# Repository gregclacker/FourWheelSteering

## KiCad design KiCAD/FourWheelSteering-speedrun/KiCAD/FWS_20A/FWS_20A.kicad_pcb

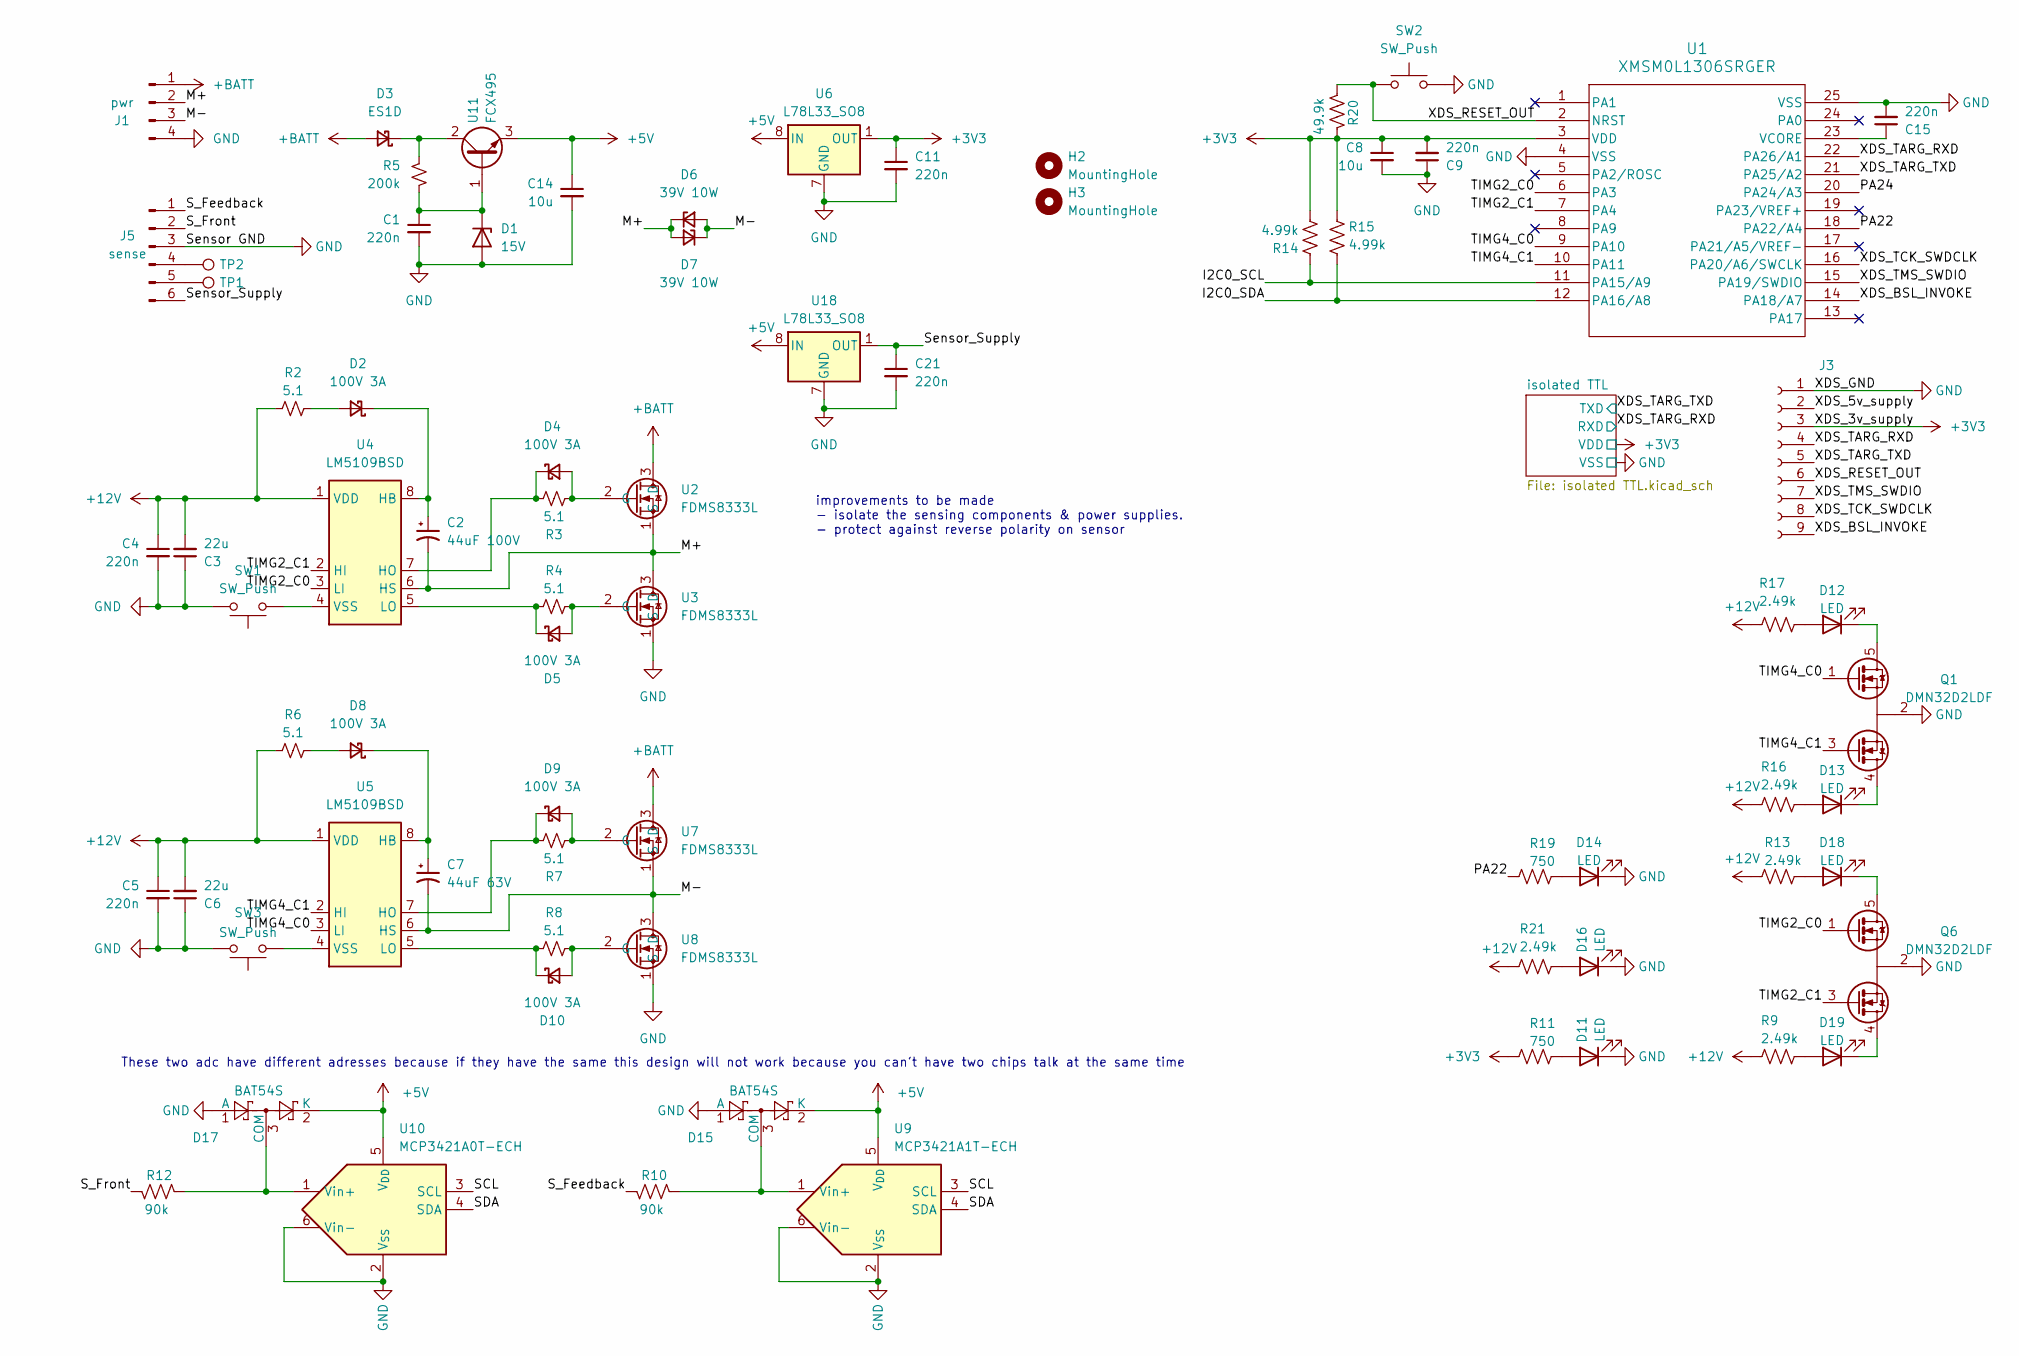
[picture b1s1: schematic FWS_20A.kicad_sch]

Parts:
C1, C4, C5, C9, C11, C15, C21: 220n; C_1206_3216Metric_Pad1.33x1.80mm_HandSolder
C2: 44uF 100V; CP_Radial_D6.3mm_P2.50mm
C3, C6: 22u; C_1206_3216Metric_Pad1.33x1.80mm_HandSolder
C7: 44uF 63V; CP_Radial_D6.3mm_P2.50mm
C8, C14: 10u; C_1206_3216Metric_Pad1.33x1.80mm_HandSolder
D1: 15V; D_SOD-123
D2, D4, D5, D8, D9, D10: 100V 3A; PMDE
D3: ES1D; D_SMA
D6, D7: 39V 10W; D_SMC_Handsoldering
D11, D12, D13, D14, D16, D18, D19: LED; LED_0603_1608Metric
D15, D17: BAT54S; SOT-23-3
H2, H3: MountingHole; MountingHole_2.2mm_M2_DIN965
J1: pwr; SolderWire-0.75sqmm_1x04_P4.8mm_D1.25mm_OD2.3mm
J3: Conn_01x09_Socket; PinHeader_1x09_P2.54mm_Vertical
J5: sense; Molex_Micro-Fit_3.0_43045-0600_2x03_P3.00mm_Horizontal
Q1, Q6: DMN32D2LDF; SOT-353_SC-70-5
R2, R3, R4, R6, R7, R8: 5.1; R_1206_3216Metric_Pad1.30x1.75mm_HandSolder
R5: 200k; R_0805_2012Metric_Pad1.20x1.40mm_HandSolder
R9, R13, R16, R17, R21: 2.49k; R_0603_1608Metric
R10, R12: 90k; R_1206_3216Metric_Pad1.30x1.75mm_HandSolder
R11, R19: 750; R_1206_3216Metric_Pad1.30x1.75mm_HandSolder
R14, R15: 4.99k; R_1206_3216Metric_Pad1.30x1.75mm_HandSolder
R20: 49.9k; R_1206_3216Metric_Pad1.30x1.75mm_HandSolder
SW1, SW3: SW_Push; SW_Push_SPST_NO_Alps_SKRK
SW2: SW_Push; SW_SPST_PTS645Sx43SMTR92
TP1, TP2: TestPoint; TestPoint_Loop_D2.50mm_Drill1.0mm_LowProfile
U1: XMSM0L1306SRGER; VQFN24_RGE_TEX
U2, U3, U7, U8: FDMS8333L; Power 56
U4, U5: LM5109BSD; WSON-8-1EP_4x4mm_P0.8mm_EP2.6x3mm
U6, U18: L78L33_SO8; SOIC-8_3.9x4.9mm_P1.27mm
U9: MCP3421A1T-ECH; SOT-23-6
U10: MCP3421A0T-ECH; SOT-23-6
U11: FCX495; SOT-89-3

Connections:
+3V3: C8.1, C9.2, C11.1, J3.3, R11.2, R14.2, R15.1, R20.1, U1.3 (VDD), U6.1 (OUT); also elsewhere on the board
+5V: C14.1, D15.2 (K), D17.2 (K), U6.8 (IN), U9.5 (V_{DD}), U10.5 (V_{DD}), U11.3, U18.8 (IN)
+12V: C3.2, C4.1, C5.1, C6.2, R2.2, R6.2, R9.2, R13.2, R16.2, R17.2, R21.2, U4.1 (VDD), U5.1 (VDD)
+BATT: D3.2 (A), J1.1, U2.3 (D), U7.3 (D)
/I2C0_SCL: R14.1, U1.11 (PA15/A9)
/I2C0_SDA: R15.2, U1.12 (PA16/A8)
/M+: C2.2, D6.1 (K), D7.2 (A), J1.2, U2.1 (S), U3.3 (D), U4.6 (HS)
/M-: C7.2, D6.2 (A), D7.1 (K), J1.3, U5.6 (HS), U7.1 (S), U8.3 (D)
/PA22: R19.2, U1.18 (PA22/A4)
/PA24: U1.20 (PA24/A3)
/SCL: U9.3 (SCL), U10.3 (SCL)
/SDA: U9.4 (SDA), U10.4 (SDA)
/S_Feedback: J5.1, R10.2
/S_Front: J5.2, R12.2
/Sensor_Supply: C21.1, J5.6, U18.1 (OUT)
/TIMG2_C0: Q6.1 (G1), U1.6 (PA3), U4.3 (LI)
/TIMG2_C1: Q6.3 (G2), U1.7 (PA4), U4.2 (HI)
/TIMG4_C0: Q1.1 (G1), U1.9 (PA10), U5.3 (LI)
/TIMG4_C1: Q1.3 (G2), U1.10 (PA11), U5.2 (HI)
/XDS_5v_supply: J3.2
/XDS_BSL_INVOKE: J3.9, U1.14 (PA18/A7)
/XDS_RESET_OUT: J3.6, R20.2, SW2.1, U1.2 (NRST)
/XDS_TARG_RXD: J3.4, U1.22 (PA26/A1); also elsewhere on the board
/XDS_TARG_TXD: J3.5, U1.21 (PA25/A2); also elsewhere on the board
/XDS_TCK_SWDCLK: J3.8, U1.16 (PA20/A6/SWCLK)
/XDS_TMS_SWDIO: J3.7, U1.15 (PA19/SWDIO)
GND: C1.2, C3.1, C4.2, C5.2, C6.1, C8.2, C9.1, C11.2, C14.2, C15.2, C21.2, D1.2 (A), D11.1 (K), D14.1 (K), D15.1 (A), D16.1 (K), D17.1 (A), J1.4, J3.1, J5.3, Q1.2 (S), Q6.2 (S), SW1.2, SW2.2, SW3.2, U1.4 (VSS), U1.25 (VSS), U3.1 (S), U6.2 (GND), U6.3 (GND), U6.6 (GND), U6.7 (GND), U8.1 (S), U9.2 (V_{SS}), U9.6 (Vin-), U10.2 (V_{SS}), U10.6 (Vin-), U18.2 (GND), U18.3 (GND), U18.6 (GND), U18.7 (GND); also elsewhere on the board
unnamed: C1.1, D1.1 (K), R5.1, U11.1
unnamed: D2.2 (A), R2.1
unnamed: C2.1, D2.1 (K), U4.8 (HB)
unnamed: D3.1 (K), R5.2, U11.2
unnamed: D4.2 (A), R3.2, U2.2 (G)
unnamed: D4.1 (K), R3.1, U4.7 (HO)
unnamed: D5.2 (A), R4.1, U3.2 (G)
unnamed: D5.1 (K), R4.2, U4.5 (LO)
unnamed: D8.2 (A), R6.1
unnamed: C7.1, D8.1 (K), U5.8 (HB)
unnamed: D9.2 (A), R7.2, U7.2 (G)
unnamed: D9.1 (K), R7.1, U5.7 (HO)
unnamed: D10.2 (A), R8.1, U8.2 (G)
unnamed: D10.1 (K), R8.2, U5.5 (LO)
unnamed: D11.2 (A), R11.1
unnamed: D12.2 (A), R17.1
unnamed: D12.1 (K), Q1.5 (D1)
unnamed: D13.2 (A), R16.1
unnamed: D13.1 (K), Q1.4 (D2)
unnamed: D14.2 (A), R19.1
unnamed: D15.3 (COM), R10.1, U9.1 (Vin+)
unnamed: D16.2 (A), R21.1
unnamed: D17.3 (COM), R12.1, U10.1 (Vin+)
unnamed: D18.2 (A), R13.1
unnamed: D18.1 (K), Q6.5 (D1)
unnamed: D19.2 (A), R9.1
unnamed: D19.1 (K), Q6.4 (D2)
unnamed: J5.4, TP2.1
unnamed: J5.5, TP1.1
unnamed: SW1.1, U4.4 (VSS), U4.9 (VSS)
unnamed: SW3.1, U5.4 (VSS), U5.9 (VSS)
unnamed: C15.1, U1.23 (VCORE)

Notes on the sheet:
These two adc have different adresses because if they have the same this design will not work because you can't have two chips talk at the same time
improvements to be made - isolate the sensing components & power supplies. - protect against reverse polarity on sensor

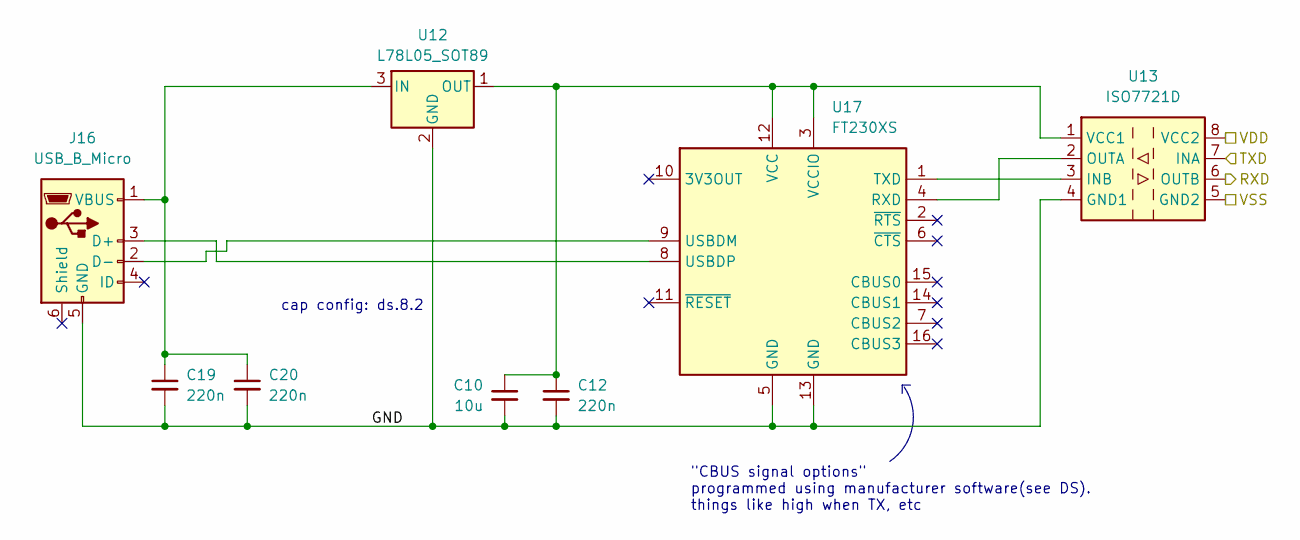
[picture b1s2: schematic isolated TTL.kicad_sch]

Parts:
C10: 10u; C_1206_3216Metric_Pad1.33x1.80mm_HandSolder
C12, C19, C20: 220n; C_1206_3216Metric_Pad1.33x1.80mm_HandSolder
J16: USB_B_Micro; USB_Micro-B_Amphenol_10118194-0001LF_Horizontal
U12: L78L05_SOT89; SOT-89-3
U13: ISO7721D; SOIC-8_3.9x4.9mm_P1.27mm
U17: FT230XS; SSOP-16_3.9x4.9mm_P0.635mm

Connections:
+3V3: U13.8 (VCC2); also elsewhere on the board
/XDS_TARG_RXD: U13.6 (OUTB); also elsewhere on the board
/XDS_TARG_TXD: U13.7 (INA); also elsewhere on the board
/isolated TTL/GND: C10.2, C12.2, C19.2, C20.2, J16.5 (GND), U12.2 (GND), U13.4 (GND1), U17.5 (GND), U17.13 (GND)
GND: U13.5 (GND2); also elsewhere on the board
unnamed: J16.3 (D+), U17.8 (USBDP)
unnamed: J16.2 (D-), U17.9 (USBDM)
unnamed: C19.1, C20.1, J16.1 (VBUS), U12.3 (IN)
unnamed: C10.1, C12.1, U12.1 (OUT), U13.1 (VCC1), U17.3 (VCCIO), U17.12 (VCC)
unnamed: U13.3 (INB), U17.1 (TXD)
unnamed: U13.2 (OUTA), U17.4 (RXD)

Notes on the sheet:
"CBUS signal options" programmed using manufacturer software(see DS). things like high when TX, etc
cap config: ds.8.2

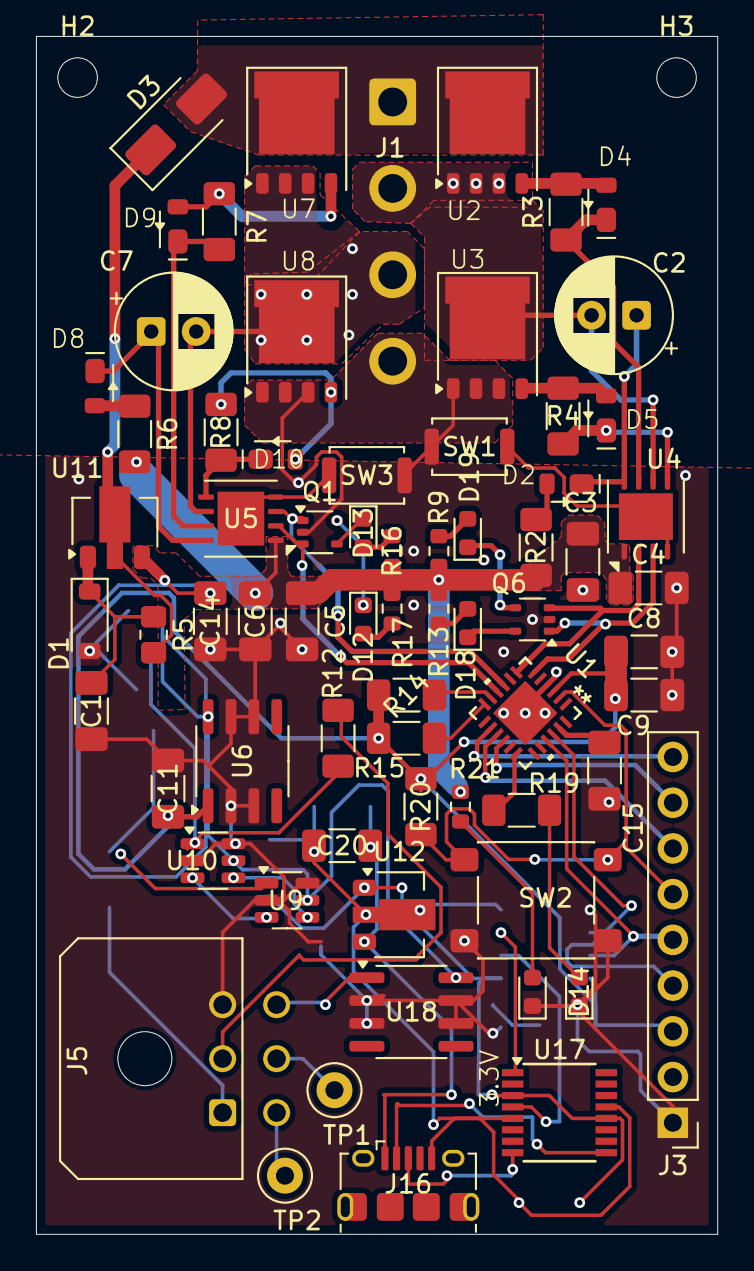
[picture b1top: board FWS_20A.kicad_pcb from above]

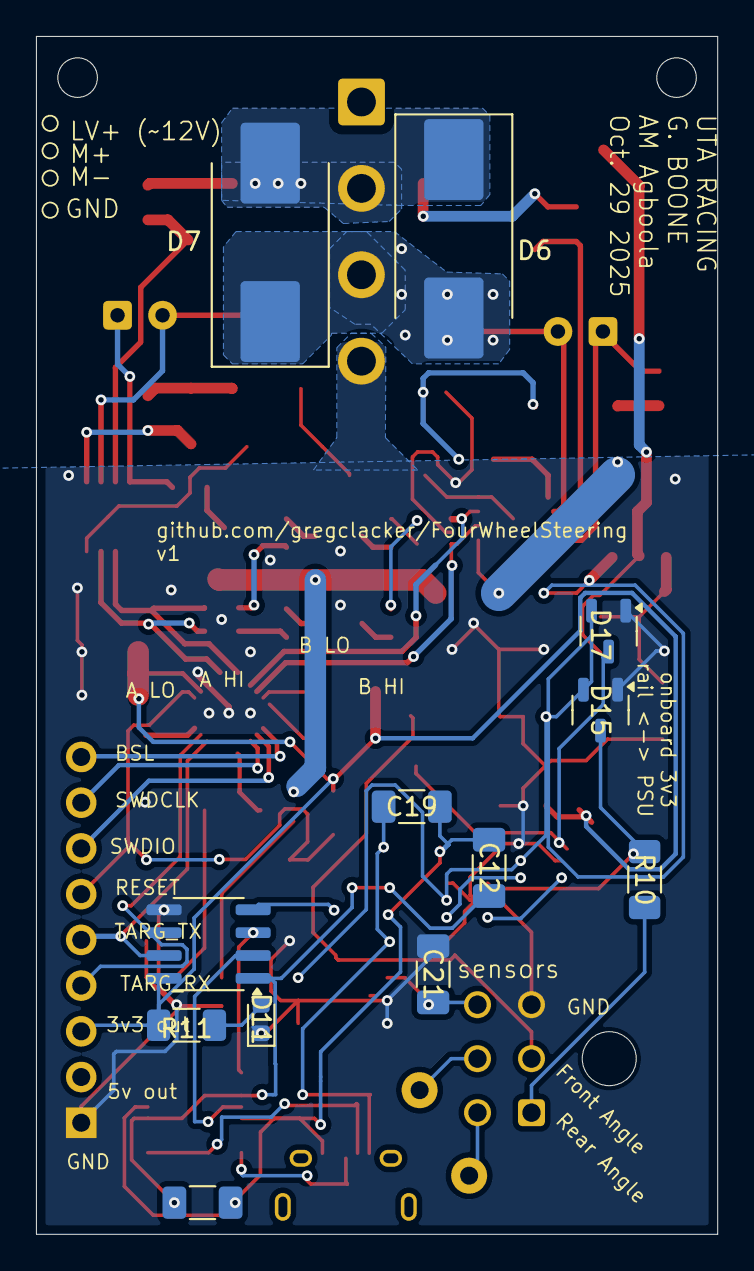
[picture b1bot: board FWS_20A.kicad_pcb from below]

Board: 2 copper layers, 37.8 x 66.5 mm, 83 parts (12 on the bottom side), 64 nets.

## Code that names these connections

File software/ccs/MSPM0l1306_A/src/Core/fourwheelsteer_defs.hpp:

/*
 * fourwheelsteer_defs.hpp
 *
 *  Created on: Nov 25, 2025
 *      Author: FSAE
 *      Drived From: https://github.com/gregclacker/FourWheelSteering/tree/main/original%20VSC%20project
 *      Contributer: Marcus Turley, Abdul-Muizz Abgoola
 */

#include <stdint.h>
#include <stdbool.h>

#include "system.hpp"

#ifndef system
#define system

/*************************************************************/

#define ESP_OK 0

//TIMG0_C0, TIMG0_C1, TIMG4_C0, TIMG4_C0
#define GATE_PIN_1         System::GPIO::PA3
#define GATE_PIN_2         System::GPIO::PA4

#define GATE_PIN_3         System::GPIO::PA10
#define GATE_PIN_4         System::GPIO::PA11

#define TIMERSYNC_REG           TIMG0
#define TIMER_REG_1             TIMG2
#define TIMER_REG_2             TIMG4

#define ADC_1_ADDR              0x49 // TODO: Update this address to match adc
#define ADC_2_ADDR              0x50

namespace System { namespace GPIO { } }

namespace FWS_Utils {

    /* NB - All this stuff is derived from the FourwheelSteering github we forked:
     * The github contains helpful front and rear wheel steer math for angles
     */
    namespace FWS {

        typedef struct {
            double WA_LW_Slope;             //This is the slope of the left wheel, wheel angle vs turn radius
            double WA_LW_Intercept;         //This is the Y intercept of the left wheel, wheel angle vs turn radius
            double WA_RW_Slope;             //This is the slope of the right wheel, wheel angle vs turn radius
            double WA_RW_Intercept;         //This is the Y intercept of the right wheel, wheel angle vs turn radius
            double TR_LW_Coefficient;       //This is the left wheel coefficient of the power function for Turn Radius vs Steering Angle
            double TR_LW_Power;             //This is the left wheel power of the power function for Turn Radius vs Steering Angle
            double TR_RW_Coefficient;       //This is the right wheel coefficient of the power function for Turn Radius vs Steering Angle
            double TR_RW_Power;             //This is the right wheel power of the power function for Turn Radius vs Steering Angle

            double KP;                      //The Kp value of the PID  | How hard motor should push
            double KI;                      //The Ki value of the PID  | Helps push motor into error range (kinda like a counter ofrce to friction)
            double KD;                      //The Kd value of the PID | Dampens movements (kinda like shock absorber)

            double sensor_max_angle;
            double sensor_angle_offset;

            double FS_SteeringAngle;        //Input Front Steering Angle, set to -91 for testing the angles, whenever actually implemented this will not have a value
            double RS_SteeringAngle;        //Input Rear Steering Angle
            double LW_Angle;                //Left Wheel Angle
            double RW_Angle;                //Right Wheel Angle
            double TR_Left;                 //Turn Radius Left Wheel Right Turn
            double TR_Right;                //Turn Radius Right Wheel Left Turn
            double IDEAL_RS_ANGLE;
            double RS_TR_RIGHT;
            double RS_WA_RIGHT;
            double RS_TR_LEFT;
            double RS_WA_LEFT;
            double RT_Percentage;
            double LT_Percentage;
            double RS_Deg;

            double deadband;

            //double Gain_Input;    //Not sure if this will be used
            //The amount of 'clicks' you want to be able to turn the rear steering adjustment knob
            int ADJUSTMENT_KNOB_VALUE;      //The value of the adjustment knob that will be used on calculations
        } FWS;

        // Basic init for FWS struct
        void INIT_FWS(FWS*);
    }

    /* NB - All this stuff is derived from the FourwheelSteering github we forked:
     * The github contains helpful front and rear wheel steer math for angles
     */
    namespace PID {
        /*
         * How to tune Ki
         * Start with:
         * Set Ki = 0
         * Tune Kp until response is fast but not unstable
         * Slowly increase Ki until the system just removes remaining error without oscillating
         * Kp reacts to now. Ki reacts to the past. Kd reacts to the future.
         */
        typedef struct {
            double kp;
            double ki;
            double kd;
            double previous_error;
            double integral;
        } PID;

        void INIT_PID(PID*, FWS::FWS*);                 // Basic init for PID struct
        double fs_pot(FWS::FWS*);                       // Front angle
        double rs_pot(FWS::FWS*);                       // Rear angle
        double caclulate_pid(PID*, double);             // Calculates PID
        double target_rear_angle(double, FWS::FWS*);    // Gets the target rear angle
    }

    /* Namespace containing general timer/pwm information
     * The general idea is to have a group of pwms contained within the 'pwms' variable for access
     * Make sure you properly set the 'pwm_count' so functions execute properly
     */
    namespace PWM {
        constexpr uint32_t PWMMAX = 0xFFFF;
        /*
         * Groups all our needed timer functionality
         */
        typedef struct {
            GPTIMER_Regs *timer;                // Timer register
            DL_TIMER_CC_INDEX cc_index;         // CC index
            const uint32_t cc_output;           // CC Output index
            const System::GPIO::GPIO pin;       // Timer Pin
            const uint32_t iomux;               // Timer IOmux
            double phase;
        } PWM;
        extern const PWM PWM_GATE_1;
        extern const PWM PWM_GATE_2;
        extern const PWM PWM_GATE_3;
        extern const PWM PWM_GATE_4;
        extern const PWM PWM_GATE_5;            // Remove this or remove it (probably forgot to remove)
        typedef struct {
            GPTIMER_Regs *timer;                // Timer register
            const PWM *pwms;                    // pwms
            const buffsize_t pwm_count;         // PWM Count
        } TIMER;
        extern const TIMER PWM_TIMER_1;
        extern const TIMER PWM_TIMER_2;

        void INIT_TIMER_BASIC(TIMER,uint32_t);  // Inits basic individual timer functionality
        void INIT_TIMER_MASTER(GPTIMER_Regs*);  // Inits basic master timer functionality through cross trigger
        void INIT_TIMER_SLAVE(TIMER,uint32_t);  // Inits basic slave timer functionality through cross trigger

        void INIT_PWM_OUTPUTS(TIMER,bool,bool);
        void INIT_PWM_OUTPUT_SLAVE(PWM,bool);
        void INIT_PWM_OUTPUT_BASIC(PWM,bool);

        void start_timers(GPTIMER_Regs**, buffsize_t, bool);
        void start_timer(GPTIMER_Regs*, bool);
        void stop_timers(GPTIMER_Regs**, buffsize_t);
        void stop_timer(GPTIMER_Regs*);

        uint32_t get_cc_output(const PWM*);         // Gets PWM output raw
        int get_duty(const PWM*);                   // Gets get PWM duty as a
        void set_duty(const PWM*, double);   // Sets PWM duty
        void set_phase(PWM *PWM, double);
        double get_phase(const PWM *PWM);
        int get_cc_phase(const PWM *PWM);

        double cc_value_ratio(double);
    }

    /* Namespace containing motor functionality
     */
    namespace Motor {
        void steer_motor(const PWM::PWM* const*, buffsize_t, FWS::FWS*);        // Steers the motor
        void motor_forward(const PWM::PWM* const*, buffsize_t, FWS::FWS*);      // Turns the motor right through the H-bridge
        void motor_backward(const PWM::PWM* const*, buffsize_t, FWS::FWS*);     // Turns the motor left through the H-bridge
        double steer_error(FWS::FWS*);                                          // Error move
    }

    /* Namespace containing adc functionality
     */
    namespace ADC {
        const bool use_external = false;        // Gets the raw binary voltage data over I2c
        void get_adc_raw(uint8_t, int16_t*);    // Gets raw the adc voltage data over I2c
        double get_adc_voltage(uint8_t);        // Gets the adc voltage over I2c
    }

    /* Namespace containing any gpio functionality
     */
    namespace GPIO {
        void INIT_GPIO(System::GPIO::GPIO);     // Inits basic GPIO functionality
    }
}

#endif

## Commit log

2025-03-26 Update
    Hardware and pinout updates
2025-04-05 Removed the error limiting
2025-04-07 PID Tuning
2025-04-08 Formatting Changes
    Removed some of the testing functions that were used to verify the controls of the system
2025-08-02 Most Recent
2025-10-01 blurb
    retuned the PID. also this project setup sucks. dont ever use VScode for this kind of stuff without instrucitons for how to set it up
2025-10-01 shuffled around files
2025-10-01 updated gitignore
2025-10-02 pwm not quite owrking
2025-10-02 good er nuff
2025-10-03 blurb
2025-10-03 unblurb
2025-10-03 we have copied all the code
2025-10-07 KiCAD Stuff
    scjsdck
2025-10-09 Updated KiCAD symbols and footprints for MSPM1306
    SDFAGD
2025-10-09 update 2
2025-10-09 lbjaec
2025-10-09 maybe schematic
2025-10-10 thanks random guy that slaved away at the lower layout
2025-10-11 cleaned a bit
2025-10-11 more silkscreen txt
2025-10-21 cleaned up a bit
2025-10-22 | 10-21-25 | Setup ADC and motor_dir Functionality |
2025-10-22 Added Helpful Comment
2025-10-23 Finished setting up UART output (Doesn't work tho)
2025-10-24 10-23-25 - Tried Fixing ADC Output (Kinda works)
2025-11-05 update for FSWA
2025-11-06 gdg
    hgr
2025-11-26 11-26-25 v0.1 Four Wheel Steer
    Will this work? idk u tell me :/
2025-12-03 12-03-25 Almost There
    - Reorganized Files
    - Added WIP ADC over I2C Functionality
    - Added WIP PWM functionlity
    - Added WIP H-Bridge Functionality
    - Replaced incorect code
2025-12-04 12-04-25
    Began finalizing PWM setup
2025-12-11 updates kicad pcb
2025-12-11 gerber files
2025-12-12 12-12-25
    - Split Timer and PWM output initialization
    - Updated/Fixed PWM structs
2025-12-13 12-13-25 Started Timer Syncronization
    - Added some potential code for TIMG timer synchronization
    - Added some new test methods
2025-12-16 12-16-25 Potential PWM Syncronization
    - Have some potential PWM synchronization with 3rd master timer TIMG0
    - Added some more preliminary motor steer code
2025-12-17 12-16-25 Restructured Program
    - Restructured some code
    - Potentially made some parts more functional, but unsure due to lack of hardware to test
2025-12-19 12-19-25 Redesigning H-Bridge
    - Started redesigning the H-Bridge Functionality
    - Started reworking Cross-trigger system
2025-12-30 12-29-25 Tweaked some PWM crosstrigger issues
2026-01-07 | Commit 23 | 01-06-26 | Marcus T. |
    - Actively testing timers in isolation
2026-01-16 | Commit 24 | 01-16-26 | Marcus Turley |
    - Presumedly got the timer sync working
    :::TIMG1 = TIMER_2
    :::TIMG2 = TIMER_4
    :::TIMA = TIMER_0
    - Began readding timer methods
2026-01-31 | Commit 25 | 01-30-26 | Marcus Turley |
    - Updated the fourwheelsteer_utils.cpp to match the barebones recoding of timersync (still not functional but hopefully will be soon)
2026-02-01 | Commit 23 | 01-31-26 | Marcus Turley |
    - Switched pin11 for pin15 for now since I don't believe it is usable for pwm on this board
    - Attempted to fix TimerSync
2026-02-05 | Commit 15 | 02-05-26 | Marcus Turley |
    - Reorganizing code to be cleaner
    - Currently pwm stuff is broken but going to fix later
2026-02-20 | Commit 17 | 02-20-26 | Marcus Turley |
    - Fixed timer issues. They work again.
    - Timersync is still broken (I believe its the fact msp0l1306 does not support TIMA)
    - Finally added PA11 (I somehow did not see the pin)
2026-02-26 | Commit 18 | Marcus Turley | 02-25-26 |
    - Attempted to add custom phase implementation (could not figure out timersync)
    - Renamed/restructured some functions
2026-03-16 sure
